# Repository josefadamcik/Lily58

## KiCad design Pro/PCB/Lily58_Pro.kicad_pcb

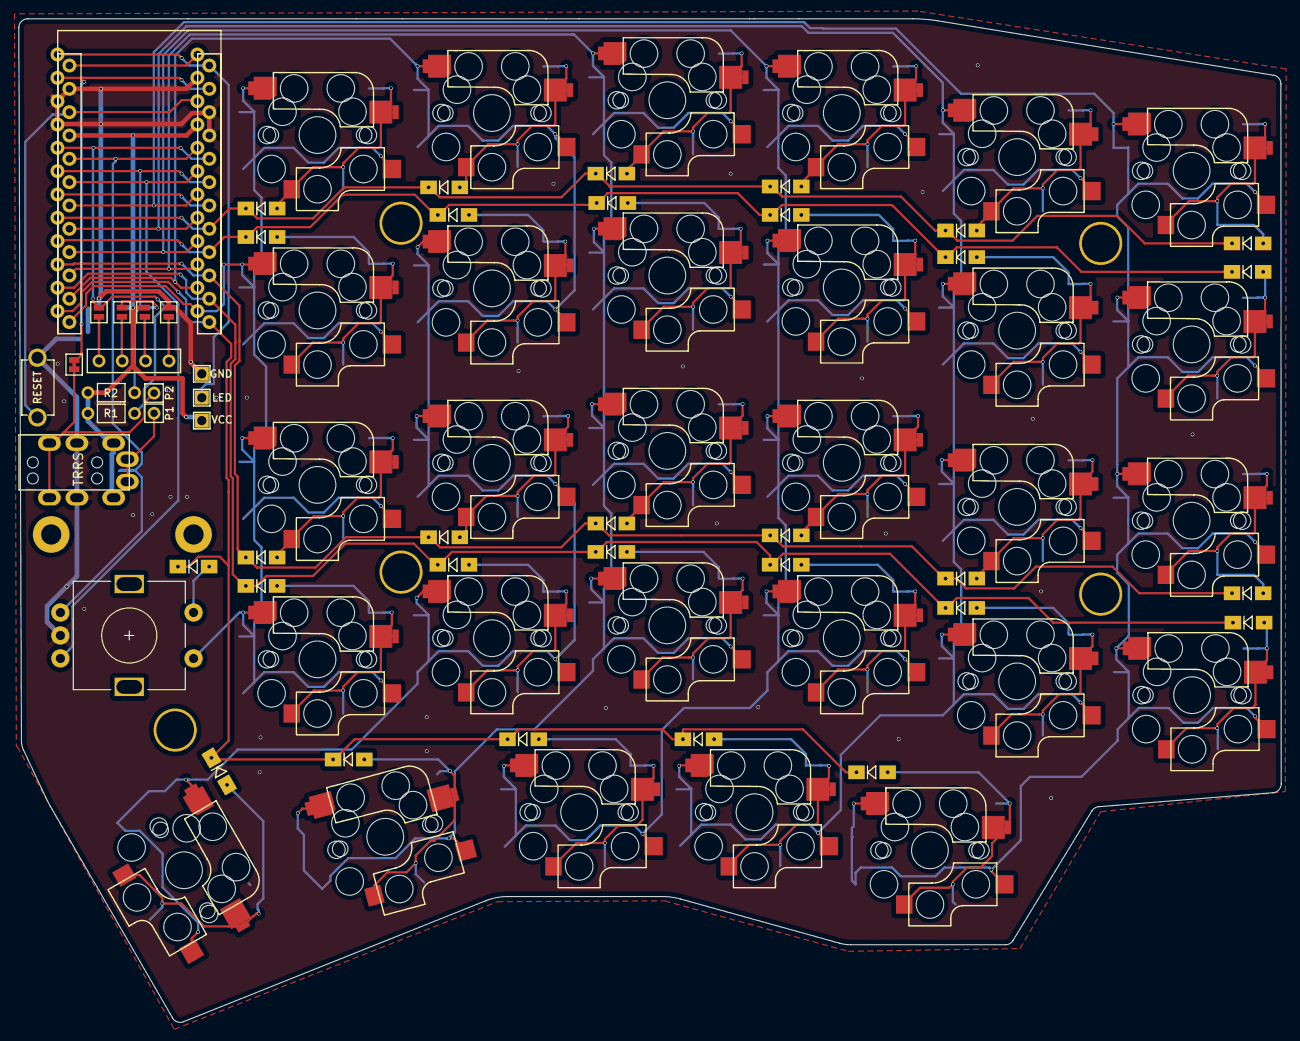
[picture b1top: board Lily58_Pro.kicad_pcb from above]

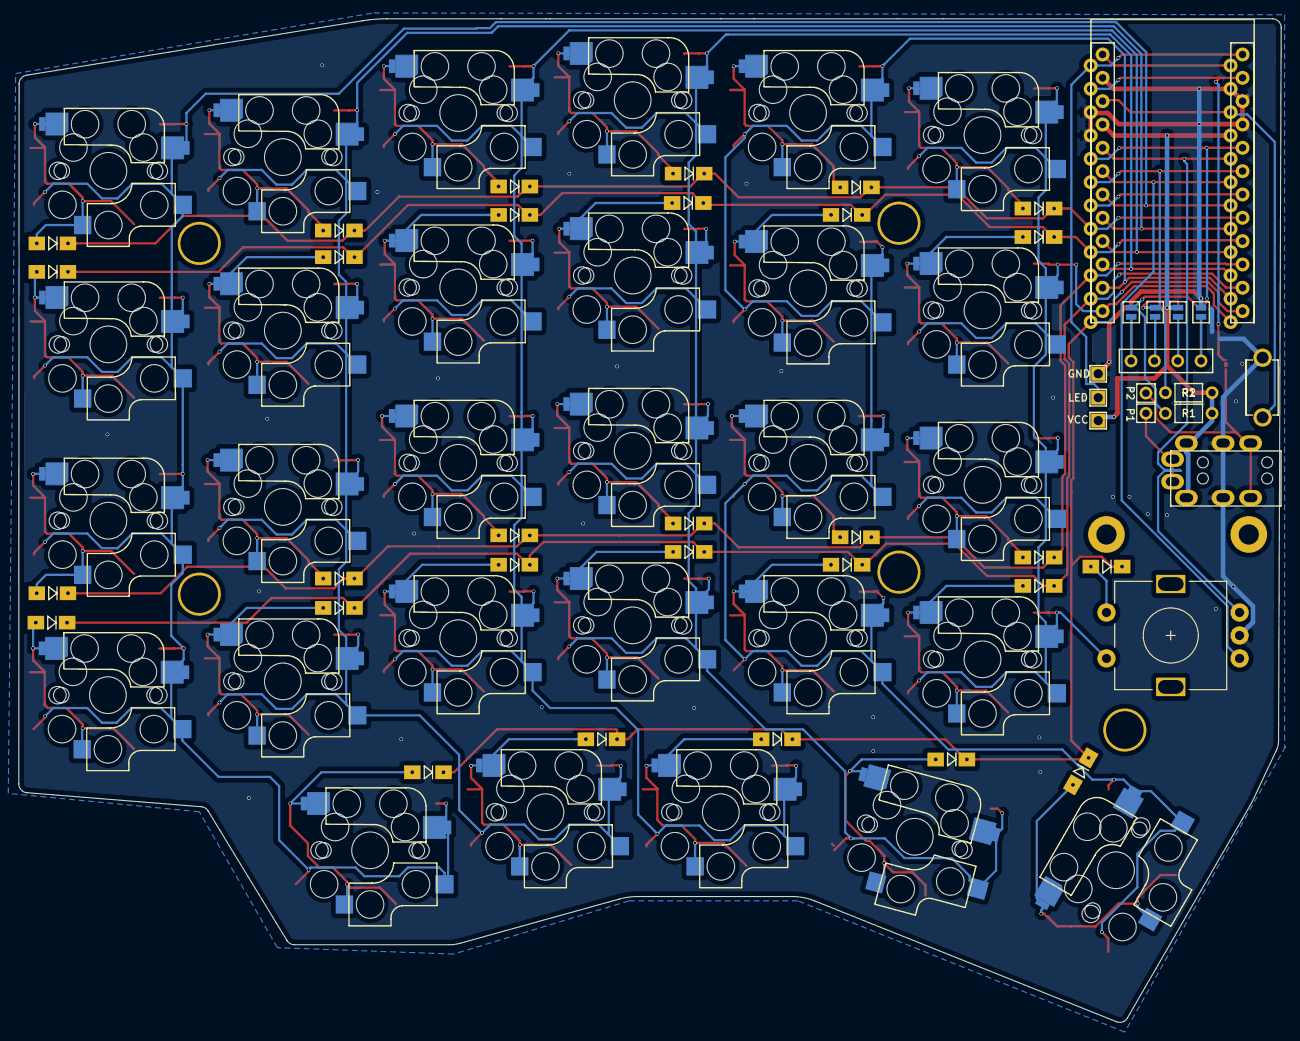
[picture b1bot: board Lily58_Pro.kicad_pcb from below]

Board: 2 copper layers, 137.5 x 109.3 mm, 85 parts (4 on the bottom side), 56 nets.

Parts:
D1, D2, D3, D4, D5, D6, D7, D8, D9, D10, D11, D12, D13, D14, D15, D16, D17, D18, D19, D20, D21, D22, D23, D24, D25, D26, D27, D28, D29, D30: D; Diode_SOD123
J1: LED
J2: 4PIN; MJ-4PP-9_rev3
J3: OLED; OLED_4Pin
JP1, JP2, JP3, JP4, JP5, JP6, JP7, JP8: Jumper_NO_Small; Jumper
P1, P2: i2c_pin; 1pin_conn
R1, R2: R; RESISTOR_mini
RSW1: SW_RST; TACT_SWITCH_TVBP06
SW1, SW2, SW3, SW4, SW5, SW6, SW7, SW8, SW9, SW10, SW11, SW12, SW13, SW14, SW15, SW16, SW17, SW18, SW19, SW20, SW21, SW22, SW23, SW24, SW27, SW28, SW29, SW30: SW_PUSH; CherryMX_KailhLowProfile_Hotswap
SW25: Rotary_Encoder_Switch; RotaryEncoder_Alps_EC11E-Switch_Vertical_H20mm-keebio_modif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
SW26: SW_PUSH; CherryMX_KailhLowProfile_Hotswap_1.5
TH1, TH2: HOLE; M2_HOLE_PCB
TH3, TH4, TH5, TH6, TH7: HOLE; HOLE_M2_TH
U1: ProMicro; ProMicro_rev2
W1: jumper; jumper_data

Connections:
/i2c_c: J2.4, P1.1
/i2c_d: J2.3, P2.1, W1.2
DATA: U1.2, W1.1
ENCA: SW25.A, U1.20
ENCB: SW25.B, U1.19
GND: J1.3, J2.2, JP1.2, JP8.2, RSW1.1, SW25.C, U1.3, U1.4, U1.23
LED: J1.2, U1.1
unnamed: D1.2, SW1.2
unnamed: D2.2, SW2.2
unnamed: D3.2, SW3.2
unnamed: D4.2, SW4.2
unnamed: D5.2, SW5.2
unnamed: D6.2, SW6.2
unnamed: D7.2, SW7.2
unnamed: D8.2, SW8.2
unnamed: D9.2, SW9.2
unnamed: D10.2, SW10.2
unnamed: D11.2, SW11.2
unnamed: D12.2, SW12.2
unnamed: D13.2, SW13.2
unnamed: D14.2, SW14.2
unnamed: D15.2, SW15.2
unnamed: D16.2, SW16.2
unnamed: D17.2, SW17.2
unnamed: D18.2, SW18.2
unnamed: D19.2, SW19.2
unnamed: D20.2, SW20.2
unnamed: D21.2, SW21.2
unnamed: D22.2, SW22.2
unnamed: D23.2, SW23.2
unnamed: D24.2, SW24.2
unnamed: D26.2, SW26.2
unnamed: D27.2, SW27.2
unnamed: D28.2, SW28.2
unnamed: D29.2, SW29.2
unnamed: D30.2, SW30.2
unnamed: J3.1, JP4.1, JP8.1
unnamed: J3.2, JP3.1, JP7.1
unnamed: J3.3, JP2.1, JP6.1
unnamed: J3.4, JP1.1, JP5.1
RESET: RSW1.2, U1.22
SCL: JP3.2, JP6.2, R2.2, U1.6
SDA: JP4.2, JP5.2, R1.2, U1.5
SW25A: SW1.1, SW7.1, SW13.1, SW19.1, SW25.S1, U1.13
SW25B: D25.2, SW25.S2
VCC: J1.1, J2.1, JP2.2, JP7.2, R1.1, R2.1, U1.21
col0: SW6.1, SW12.1, SW18.1, SW24.1, SW30.1, U1.18
col1: SW5.1, SW11.1, SW17.1, SW23.1, SW29.1, U1.17
col2: SW4.1, SW10.1, SW16.1, SW22.1, SW28.1, U1.16
col3: SW3.1, SW9.1, SW15.1, SW21.1, SW27.1, U1.15
col4: SW2.1, SW8.1, SW14.1, SW20.1, SW26.1, U1.14
row0: D1.1, D2.1, D3.1, D4.1, D5.1, D6.1, U1.8
row1: D7.1, D8.1, D9.1, D10.1, D11.1, D12.1, U1.9
row2: D13.1, D14.1, D15.1, D16.1, D17.1, D18.1, U1.10
row3: D19.1, D20.1, D21.1, D22.1, D23.1, D24.1, U1.11
row4: D25.1, D26.1, D27.1, D28.1, D29.1, D30.1, U1.12

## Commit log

2019-09-22 Make the project editable
2019-09-22 Add missing fooprints from the board
2019-09-22 Fix outline.
2019-09-22 Update footprints a bit, remove some DRC errors (at least we have less of the).
2019-09-22 Add another switch.
2019-09-22 Add outline svg
2019-09-22 Replace Edeg-Cut with new one.
2019-09-25 Add rotary encoder, update pcb WIP.
2019-09-25 Working on routing
2019-09-25 Working on routing 2
2019-09-25 Routing completed.
2019-09-25 Update shape
2019-09-28 First drawft, more work on the shape
2019-09-28 Better edge shape, copper pour vias, better drill holes
